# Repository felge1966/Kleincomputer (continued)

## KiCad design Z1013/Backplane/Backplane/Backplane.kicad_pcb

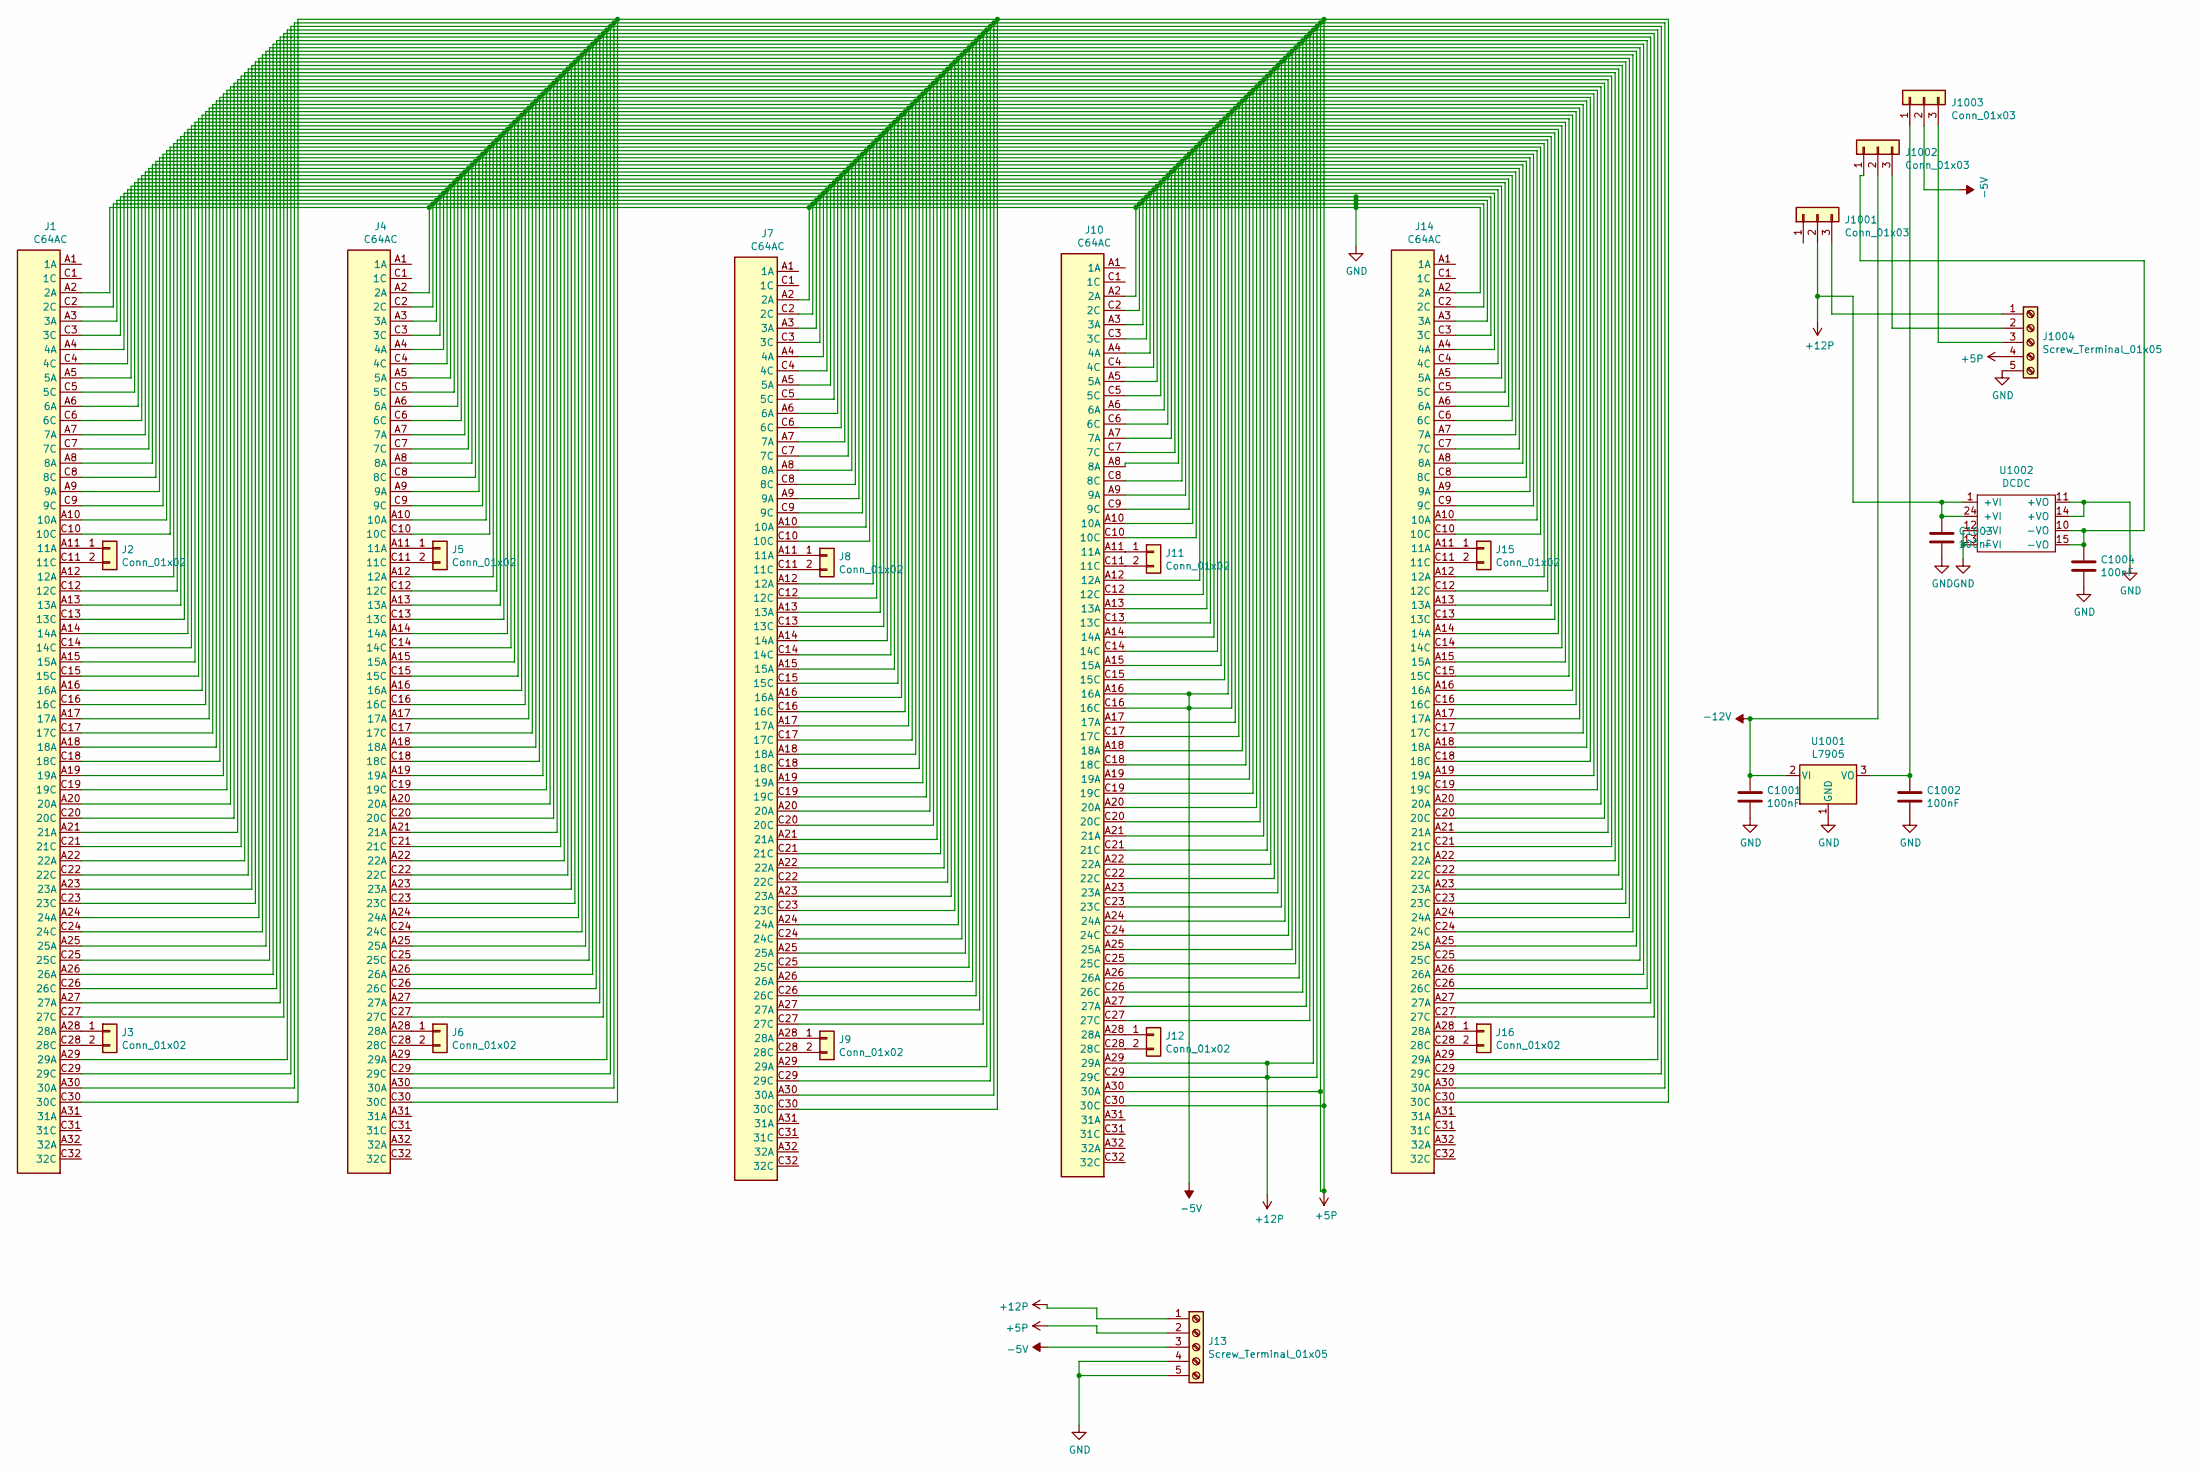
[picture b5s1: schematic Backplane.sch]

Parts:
C1001, C1002, C1003, C1004: 100nF; C_Disc_D3.0mm_W2.0mm_P2.50mm
J1, J4, J7, J10, J14: C64AC; DIN41612_C_3x32_Female_Vertical_THT-Gross_K1520
J2, J3, J5, J6, J8, J9, J11, J12, J15, J16: Conn_01x02; PinSocket_1x02_P2.54mm_Vertical
J13, J1004: Screw_Terminal_01x05; JST_EH_B5B-EH-A_1x05_P2.50mm_Vertical
J1001, J1002, J1003: Conn_01x03; PinHeader_1x03_P2.54mm_Vertical
U1001: L7905; TO-220-3_Horizontal_TabUp
U1002: DCDC; DIP-24_W15.24mm_LongPads

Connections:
+5P: J1.A30 (30A), J1.C30 (30C), J4.A30 (30A), J4.C30 (30C), J7.A30 (30A), J7.C30 (30C), J10.A30 (30A), J10.C30 (30C), J13.2, J14.A30 (30A), J14.C30 (30C), J1004.4
+12P: C1003.1, J1.A29 (29A), J1.C29 (29C), J4.A29 (29A), J4.C29 (29C), J7.A29 (29A), J7.C29 (29C), J10.A29 (29A), J10.C29 (29C), J13.1, J14.A29 (29A), J14.C29 (29C), J1001.2, U1002.1 (+VI), U1002.24 (+VI)
-5V: J1.A16 (16A), J1.C16 (16C), J4.A16 (16A), J4.C16 (16C), J7.A16 (16A), J7.C16 (16C), J10.A16 (16A), J10.C16 (16C), J13.3, J14.A16 (16A), J14.C16 (16C), J1003.2
-12V: C1001.1, J1002.2, U1001.2 (VI)
GND: C1001.2, C1002.2, C1003.2, C1004.2, J1.A2 (2A), J1.A3 (3A), J1.C2 (2C), J1.C3 (3C), J4.A2 (2A), J4.A3 (3A), J4.C2 (2C), J4.C3 (3C), J7.A2 (2A), J7.A3 (3A), J7.C2 (2C), J7.C3 (3C), J10.A2 (2A), J10.A3 (3A), J10.C2 (2C), J10.C3 (3C), J13.4, J13.5, J14.A2 (2A), J14.A3 (3A), J14.C2 (2C), J14.C3 (3C), J1004.5, U1001.1 (GND), U1002.11 (+VO), U1002.12 (-VI), U1002.13 (-VI), U1002.14 (+VO)
unnamed: C1002.1, J1003.1, U1001.3 (VO)
unnamed: C1004.1, J1002.1, U1002.10 (-VO), U1002.15 (-VO)
unnamed: J1.A4 (4A), J4.A4 (4A), J7.A4 (4A), J10.A4 (4A), J14.A4 (4A)
unnamed: J1.A5 (5A), J4.A5 (5A), J7.A5 (5A), J10.A5 (5A), J14.A5 (5A)
unnamed: J1.A6 (6A), J4.A6 (6A), J7.A6 (6A), J10.A6 (6A), J14.A6 (6A)
unnamed: J1.A7 (7A), J4.A7 (7A), J7.A7 (7A), J10.A7 (7A), J14.A7 (7A)
unnamed: J1.A8 (8A), J4.A8 (8A), J7.A8 (8A), J10.A8 (8A), J14.A8 (8A)
unnamed: J1.A9 (9A), J4.A9 (9A), J7.A9 (9A), J10.A9 (9A), J14.A9 (9A)
unnamed: J1.A10 (10A), J4.A10 (10A), J7.A10 (10A), J10.A10 (10A), J14.A10 (10A)
unnamed: J1.A11 (11A), J2.1
unnamed: J1.A12 (12A), J4.A12 (12A), J7.A12 (12A), J10.A12 (12A), J14.A12 (12A)
unnamed: J1.A13 (13A), J4.A13 (13A), J7.A13 (13A), J10.A13 (13A), J14.A13 (13A)
unnamed: J1.A14 (14A), J4.A14 (14A), J7.A14 (14A), J10.A14 (14A), J14.A14 (14A)
unnamed: J1.A15 (15A), J4.A15 (15A), J7.A15 (15A), J10.A15 (15A), J14.A15 (15A)
unnamed: J1.A17 (17A), J4.A17 (17A), J7.A17 (17A), J10.A17 (17A), J14.A17 (17A)
unnamed: J1.A18 (18A), J4.A18 (18A), J7.A18 (18A), J10.A18 (18A), J14.A18 (18A)
unnamed: J1.A19 (19A), J4.A19 (19A), J7.A19 (19A), J10.A19 (19A), J14.A19 (19A)
unnamed: J1.A20 (20A), J4.A20 (20A), J7.A20 (20A), J10.A20 (20A), J14.A20 (20A)
unnamed: J1.A21 (21A), J4.A21 (21A), J7.A21 (21A), J10.A21 (21A), J14.A21 (21A)
unnamed: J1.A22 (22A), J4.A22 (22A), J7.A22 (22A), J10.A22 (22A), J14.A22 (22A)
unnamed: J1.A23 (23A), J4.A23 (23A), J7.A23 (23A), J10.A23 (23A), J14.A23 (23A)
unnamed: J1.A24 (24A), J4.A24 (24A), J7.A24 (24A), J10.A24 (24A), J14.A24 (24A)
unnamed: J1.A25 (25A), J4.A25 (25A), J7.A25 (25A), J10.A25 (25A), J14.A25 (25A)
unnamed: J1.A26 (26A), J4.A26 (26A), J7.A26 (26A), J10.A26 (26A), J14.A26 (26A)
unnamed: J1.A27 (27A), J4.A27 (27A), J7.A27 (27A), J10.A27 (27A), J14.A27 (27A)
unnamed: J1.A28 (28A), J3.1
unnamed: J1.C4 (4C), J4.C4 (4C), J7.C4 (4C), J10.C4 (4C), J14.C4 (4C)
unnamed: J1.C5 (5C), J4.C5 (5C), J7.C5 (5C), J10.C5 (5C), J14.C5 (5C)
unnamed: J1.C6 (6C), J4.C6 (6C), J7.C6 (6C), J10.C6 (6C), J14.C6 (6C)
unnamed: J1.C7 (7C), J4.C7 (7C), J7.C7 (7C), J10.C7 (7C), J14.C7 (7C)
unnamed: J1.C8 (8C), J4.C8 (8C), J7.C8 (8C), J10.C8 (8C), J14.C8 (8C)
unnamed: J1.C9 (9C), J4.C9 (9C), J7.C9 (9C), J10.C9 (9C), J14.C9 (9C)
unnamed: J1.C10 (10C), J4.C10 (10C), J7.C10 (10C), J10.C10 (10C), J14.C10 (10C)
unnamed: J1.C11 (11C), J2.2
unnamed: J1.C12 (12C), J4.C12 (12C), J7.C12 (12C), J10.C12 (12C), J14.C12 (12C)
unnamed: J1.C13 (13C), J4.C13 (13C), J7.C13 (13C), J10.C13 (13C), J14.C13 (13C)
unnamed: J1.C14 (14C), J4.C14 (14C), J7.C14 (14C), J10.C14 (14C), J14.C14 (14C)
unnamed: J1.C15 (15C), J4.C15 (15C), J7.C15 (15C), J10.C15 (15C), J14.C15 (15C)
unnamed: J1.C17 (17C), J4.C17 (17C), J7.C17 (17C), J10.C17 (17C), J14.C17 (17C)
unnamed: J1.C18 (18C), J4.C18 (18C), J7.C18 (18C), J10.C18 (18C), J14.C18 (18C)
unnamed: J1.C19 (19C), J4.C19 (19C), J7.C19 (19C), J10.C19 (19C), J14.C19 (19C)
unnamed: J1.C20 (20C), J4.C20 (20C), J7.C20 (20C), J10.C20 (20C), J14.C20 (20C)
unnamed: J1.C21 (21C), J4.C21 (21C), J7.C21 (21C), J10.C21 (21C), J14.C21 (21C)
unnamed: J1.C22 (22C), J4.C22 (22C), J7.C22 (22C), J10.C22 (22C), J14.C22 (22C)
unnamed: J1.C23 (23C), J4.C23 (23C), J7.C23 (23C), J10.C23 (23C), J14.C23 (23C)
unnamed: J1.C24 (24C), J4.C24 (24C), J7.C24 (24C), J10.C24 (24C), J14.C24 (24C)
unnamed: J1.C25 (25C), J4.C25 (25C), J7.C25 (25C), J10.C25 (25C), J14.C25 (25C)
unnamed: J1.C26 (26C), J4.C26 (26C), J7.C26 (26C), J10.C26 (26C), J14.C26 (26C)
unnamed: J1.C27 (27C), J4.C27 (27C), J7.C27 (27C), J10.C27 (27C), J14.C27 (27C)
unnamed: J1.C28 (28C), J3.2
unnamed: J4.A11 (11A), J5.1
unnamed: J4.A28 (28A), J6.1
unnamed: J4.C11 (11C), J5.2
unnamed: J4.C28 (28C), J6.2
unnamed: J7.A11 (11A), J8.1
unnamed: J7.A28 (28A), J9.1
unnamed: J7.C11 (11C), J8.2
unnamed: J7.C28 (28C), J9.2
unnamed: J10.A11 (11A), J11.1
unnamed: J10.A28 (28A), J12.1
unnamed: J10.C11 (11C), J11.2
unnamed: J10.C28 (28C), J12.2
unnamed: J14.A11 (11A), J15.1
unnamed: J14.A28 (28A), J16.1
unnamed: J14.C11 (11C), J15.2
unnamed: J14.C28 (28C), J16.2
unnamed: J1001.3, J1004.1
unnamed: J1002.3, J1004.2
unnamed: J1003.3, J1004.3

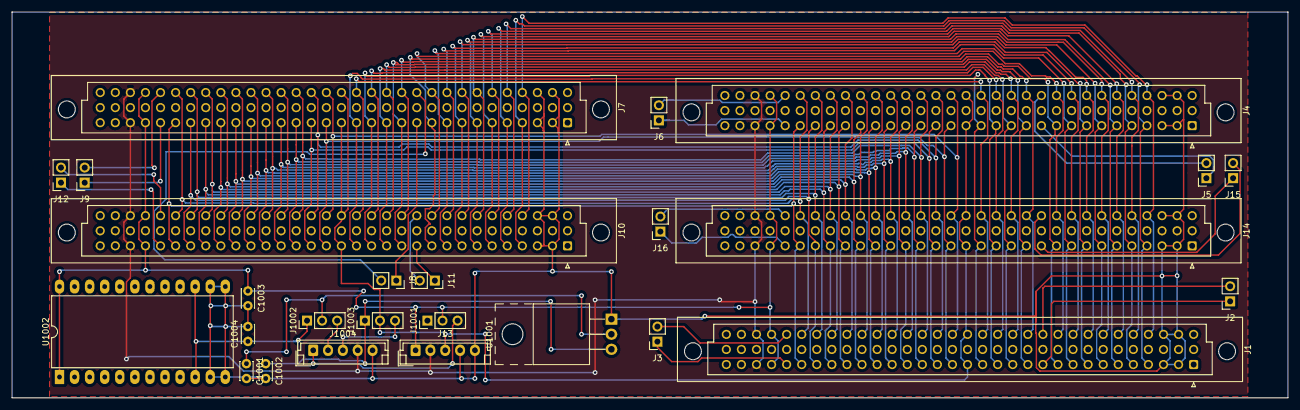
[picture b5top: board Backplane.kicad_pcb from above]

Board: 2 copper layers, 215.0 x 65.0 mm, 26 parts (0 on the bottom side), 74 nets.

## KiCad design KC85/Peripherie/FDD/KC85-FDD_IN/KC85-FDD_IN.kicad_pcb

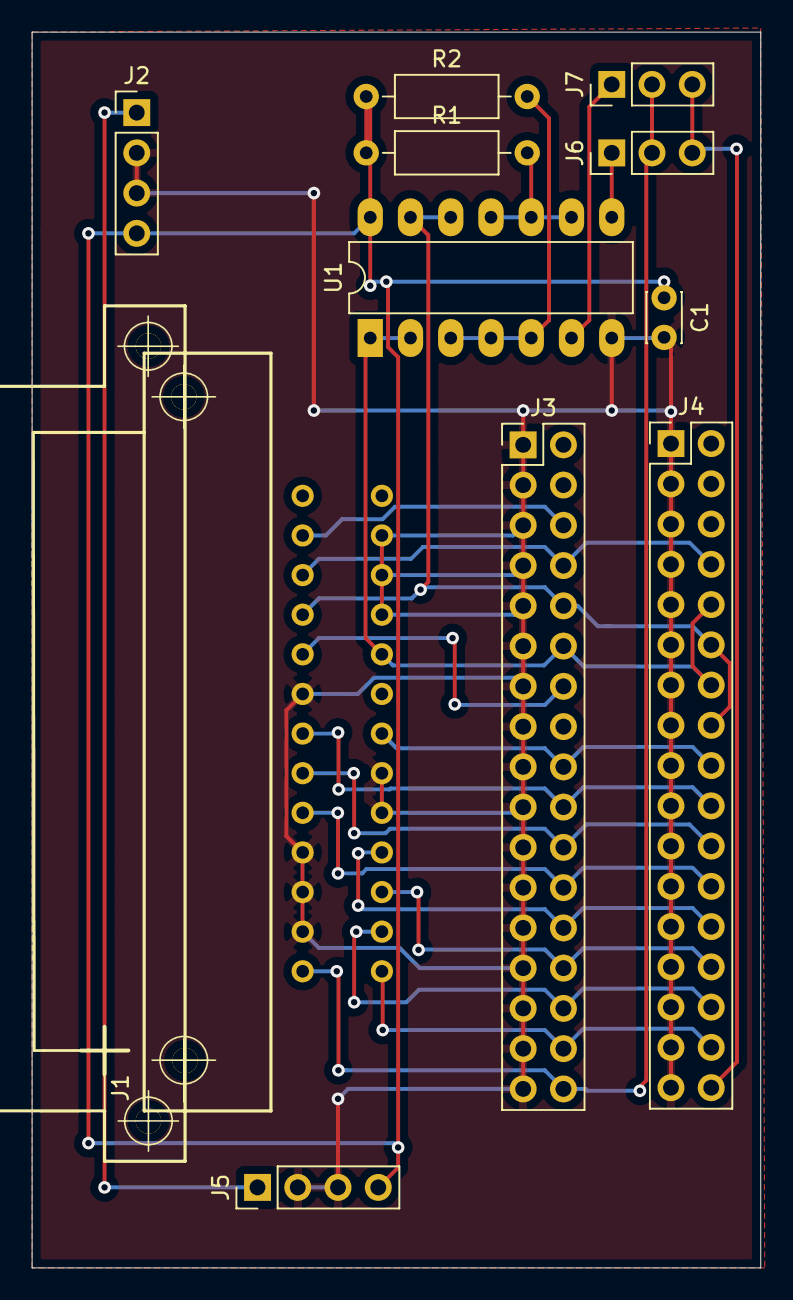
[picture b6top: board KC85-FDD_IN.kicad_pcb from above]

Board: 2 copper layers, 46.0 x 78.0 mm, 11 parts (0 on the bottom side), 22 nets.

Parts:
C1: 100n; C_Disc_D3.0mm_W2.0mm_P2.50mm
J1: Conn_02x13_Row_Letter_First; EFS2x13_DIN_male_a1
J2, J5: Conn_01x04; PinHeader_1x04_P2.54mm_Vertical
J3: IC; PinHeader_2x17_P2.54mm_Vertical
J4: Drive; PinHeader_2x17_P2.54mm_Vertical
J6: RDY-SE0; PinHeader_1x03_P2.54mm_Vertical
J7: RDY-SE1; PinHeader_1x03_P2.54mm_Vertical
R1, R2: 1K; R_Axial_DIN0207_L6.3mm_D2.5mm_P10.16mm_Horizontal
U1: 74LS03; DIP-14_W7.62mm_LongPads

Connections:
+5P: C1.1, J2.4, J5.4, R1.1, R2.1, U1.14
+12P: J2.1, J5.1
GND: C1.2, J1.a6, J1.a10, J1.a11, J1.a12, J1.b2, J1.b3, J1.b4, J1.b8, J1.b9, J2.2, J2.3, J3.1, J3.3, J3.5, J3.7, J3.9, J3.11, J3.13, J3.15, J3.17, J3.19, J3.21, J3.23, J3.25, J3.27, J3.29, J3.31, J3.33, J4.1, J4.3, J4.5, J4.7, J4.9, J4.11, J4.13, J4.15, J4.17, J4.19, J4.21, J4.23, J4.25, J4.27, J4.29, J4.31, J4.33, J5.2, J5.3, U1.7
IX: J1.a3, J3.8, J4.8
unnamed: J4.34, J6.3, J7.3
unnamed: J6.1, U1.8
unnamed: J7.1, U1.6
unnamed: R1.2, U1.9, U1.10, U1.11
unnamed: R2.2, U1.3, U1.4, U1.5
RD: J1.b12, J3.30, J4.30
RDY: J1.a13, J3.34, J6.2, J7.2
SD: J1.b7, J3.18, J4.18
SE0: J1.a4, J3.10, J4.12, J4.16, U1.12, U1.13
SE1: J1.b5, J3.12, J4.10, J4.14, U1.1, U1.2
SE2: J1.a5, J3.14
SE3: J1.a2, J3.6
SS: J1.b13, J3.32, J4.32
ST: J1.a7, J3.20, J4.20
T0: J1.b10, J3.26, J4.26
WD: J1.a8, J3.22, J4.22
WE: J1.a9, J3.24, J4.24
WP: J1.b11, J3.28, J4.28

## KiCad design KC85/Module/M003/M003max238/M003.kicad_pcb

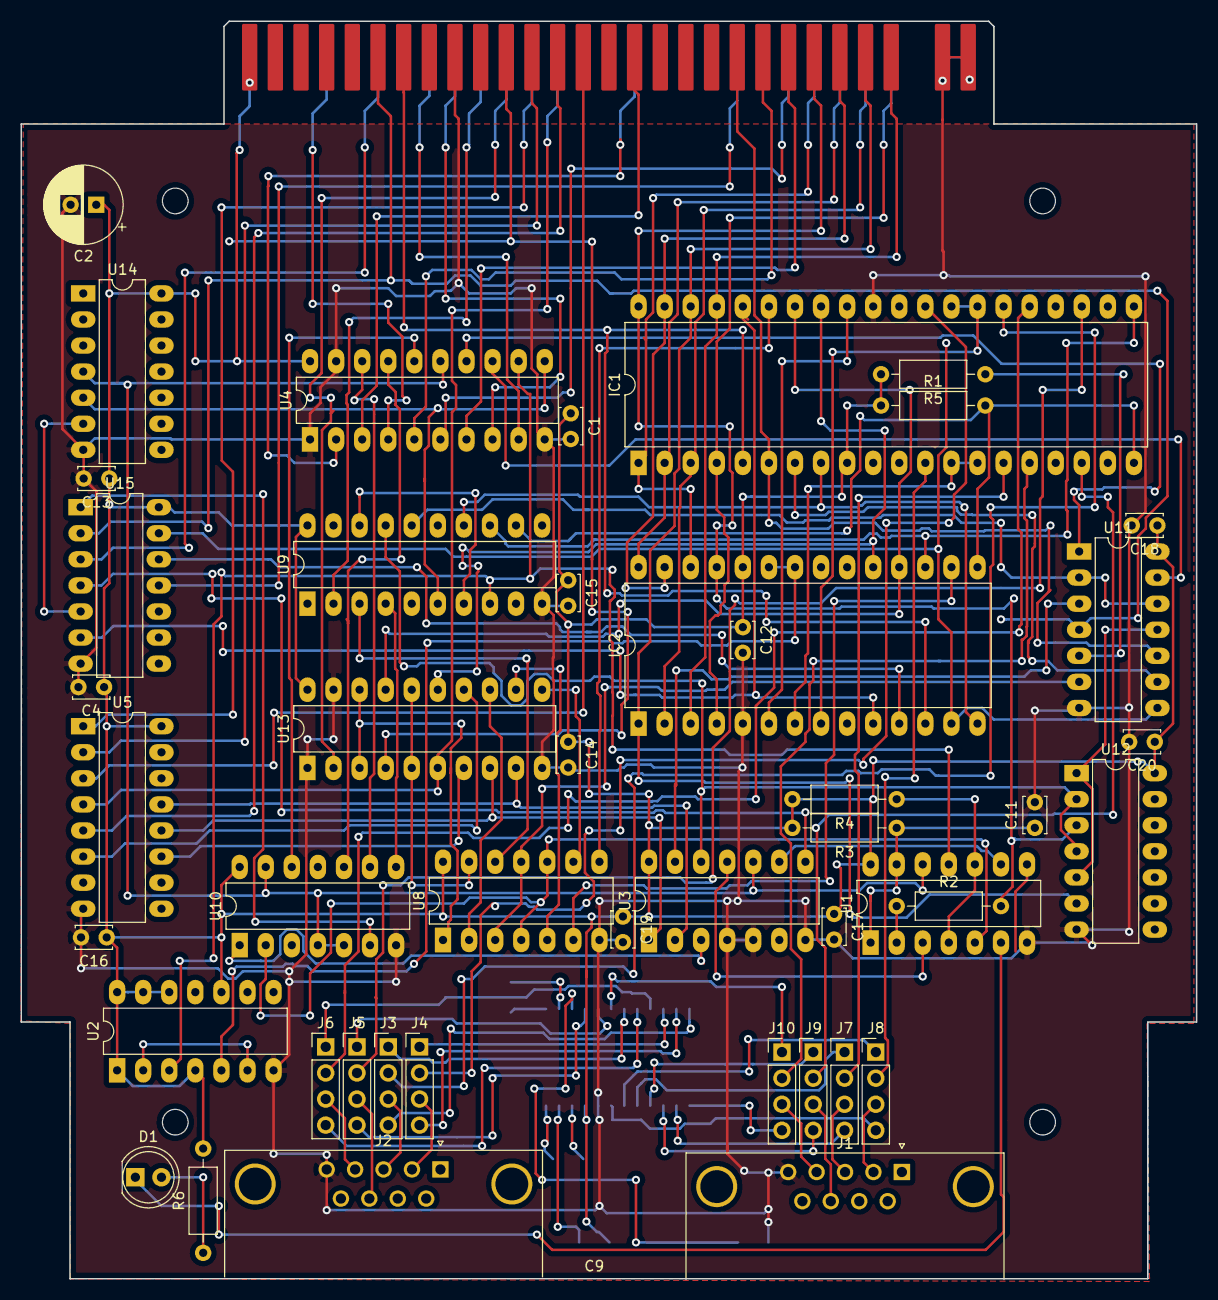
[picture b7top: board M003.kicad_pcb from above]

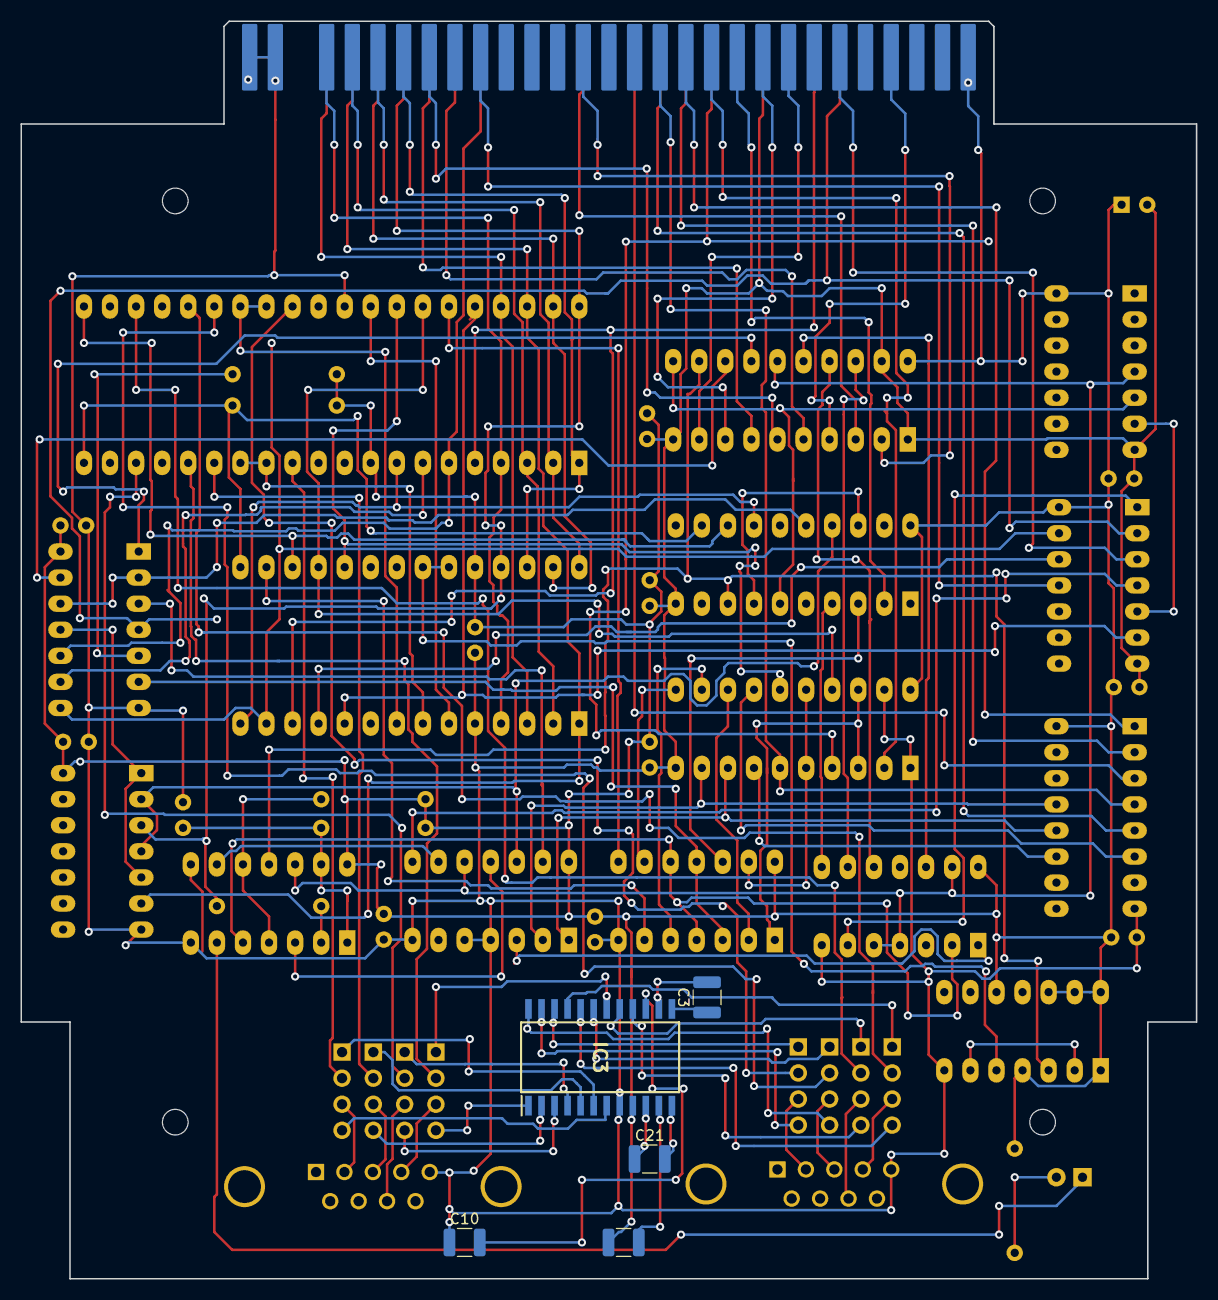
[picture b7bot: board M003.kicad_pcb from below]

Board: 2 copper layers, 114.5 x 122.5 mm, 51 parts (5 on the bottom side), 123 nets.

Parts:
C1, C4, C12, C13, C14, C15, C16, C17, C18, C19, C20: 22nF; C_Disc_D3.4mm_W2.1mm_P2.50mm
C2: 560µ; CP_Radial_D7.5mm_P2.50mm
C3, C9, C10, C21: 1µ; C_1210_3225Metric
C11: 100n; C_Disc_D3.4mm_W2.1mm_P2.50mm
D1: LED; LED_D5.0mm
IC1: SIO2-DIP-40; DIP-40_W15.24mm_LongPads
IC2: CTC-DIP-28; DIP-28_W15.24mm_LongPads
IC3: MAX238CWG+; SOIC127P1032X265-24N
J1: SER1; DSUB-9_Female_Horizontal_P2.77x2.84mm_EdgePinOffset7.70mm_H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
J2: SER2; DSUB-9_Female_Horizontal_P2.77x2.84mm_EdgePinOffset7.70mm_H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
J3: TXD2; PinHeader_1x04_P2.54mm_Vertical
J4: RxD2; PinHeader_1x04_P2.54mm_Vertical
J5: CTS2; PinHeader_1x04_P2.54mm_Vertical
J6: DTR2; PinHeader_1x04_P2.54mm_Vertical
J7: TXD1; PinHeader_1x04_P2.54mm_Vertical
J8: RxD1; PinHeader_1x04_P2.54mm_Vertical
J9: CTS1; PinHeader_1x04_P2.54mm_Vertical
J10: DTR1; PinHeader_1x04_P2.54mm_Vertical
R1: 620; R_Axial_DIN0207_L6.3mm_D2.5mm_P10.16mm_Horizontal
R2: 100R; R_Axial_DIN0207_L6.3mm_D2.5mm_P10.16mm_Horizontal
R3, R4, R5: 2K2; R_Axial_DIN0207_L6.3mm_D2.5mm_P10.16mm_Horizontal
R6: 390R; R_Axial_DIN0207_L6.3mm_D2.5mm_P10.16mm_Horizontal
U1, U2: 74LS74; DIP-14_W7.62mm_LongPads
U3, U14: 74LS00; DIP-14_W7.62mm_LongPads
U4, U9, U13: 74LS540; DIP-20_W7.62mm_LongPads
U5: 74LS138; DIP-16_W7.62mm_LongPads
U8: 74LS10; DIP-14_W7.62mm_LongPads
U10: 74LS20; DIP-14_W7.62mm_LongPads
U11, U15: 74LS08; DIP-14_W7.62mm_LongPads
U12: 74LS03; DIP-14_W7.62mm_LongPads
XM1: KC85_Modulsteckverbinder; KC85_Modul

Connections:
+5P: C1.1, C2.1, C4.1, C9.2, C12.1, C13.1, C14.1, C15.1, C16.1, C17.1, C18.1, C19.1, C20.1, IC1.9, IC2.24, IC3.9, R1.1, R3.2, R4.2, R5.2, R6.2, U1.14, U2.1, U2.4, U2.10, U2.12, U2.13, U2.14, U3.14, U4.20, U5.16, U8.14, U9.20, U10.14, U11.14, U12.14, U13.20, U14.14, U15.14, XM1.29A, XM1.29B
AB0: U13.2, XM1.19A
AB1: U13.4, XM1.19B
AB2: U5.1, XM1.18A
AB3: U5.2, XM1.18B
AB4: U5.4, U13.6, XM1.17A
AB5: U5.5, XM1.17B
AB7: U5.3, XM1.16B
AB8: U4.2, XM1.14A
AB9: U4.3, XM1.14B
CTSA: IC1.18, J9.2
CTSB: IC1.23, J5.2
DB0: IC1.40, IC2.25, R2.2, U12.3, XM1.7B
DB1: IC1.1, IC2.26, XM1.7A
DB2: IC1.39, IC2.27, XM1.6B
DB3: IC1.2, IC2.28, XM1.6A
DB4: IC1.38, IC2.1, U12.6, XM1.5B
DB5: IC1.3, IC2.2, XM1.5A
DB6: IC1.37, IC2.3, XM1.4B
DB7: IC1.4, IC2.4, XM1.4A
DTRA: IC1.16, J10.2
DTRB: IC1.25, J6.2
GND: C1.2, C2.2, C4.2, C10.1, C11.2, C12.2, C13.2, C14.2, C15.2, C16.2, C17.2, C18.2, C19.2, C20.2, IC1.31, IC2.5, IC3.8, J1.5, J2.5, U1.7, U2.7, U3.4, U3.5, U3.7, U4.1, U4.10, U4.19, U5.8, U8.7, U9.10, U10.7, U11.7, U12.7, U13.1, U13.10, U13.19, U14.7, U15.7, XM1.1A, XM1.1B, XM1.2A, XM1.2B, XM1.21B
IEI: IC1.6, U11.10, XM1.10B
IEO: U15.11, XM1.10A
MEI: U11.4, U15.2, XM1.24B
MEO: U15.3, XM1.24A
N09: U1.12, U3.10, U4.15, U10.4, U10.5, U10.13, U14.4
N12: IC1.32, IC2.6
N13: IC1.20, IC2.15, R1.2, U9.12
N14: U14.6, U15.5
N15: IC1.8, IC2.14, U9.14
N16: IC1.21, IC2.17, U9.13
N20: IC1.34, IC2.18, U13.17
N21: IC1.33, IC2.19, U13.15
N24: U1.11, U2.3, U4.12, U9.8
N25: IC1.36, IC2.10, U15.6
N33: IC2.22, IC2.23, U2.5
unnamed: C3.1, IC3.13
unnamed: C3.2, IC3.14
unnamed: C9.1, IC3.11
unnamed: C10.2, IC3.15
unnamed: C11.1, R3.1, U1.1, U1.13
unnamed: C21.1, IC3.10
unnamed: C21.2, IC3.12
unnamed: D1.1, U1.6
unnamed: D1.2, R6.1
unnamed: IC1.7, U11.9
unnamed: IC1.13, IC1.14, IC2.7
unnamed: IC1.27, IC1.28, IC2.8
unnamed: IC1.35, U8.8
unnamed: IC2.11, U15.12
unnamed: IC2.13, U11.8, U15.13
unnamed: IC2.16, U8.6
unnamed: IC3.1, J10.4
unnamed: IC3.2, J7.4
unnamed: IC3.3, J9.4
unnamed: IC3.4, J9.1
unnamed: IC3.5, J7.1
unnamed: IC3.6, J8.1
unnamed: IC3.7, J8.4
unnamed: IC3.16, J5.4
unnamed: IC3.17, J5.1
unnamed: IC3.18, J10.1
unnamed: IC3.19, J3.1
unnamed: IC3.20, J6.4
unnamed: IC3.21, J6.1
unnamed: IC3.22, J4.1
unnamed: IC3.23, J4.4
unnamed: IC3.24, J3.4
unnamed: J1.2, J8.3
unnamed: J1.3, J7.3
unnamed: J1.4, J10.3
unnamed: J1.8, J9.3
unnamed: J2.2, J4.3
unnamed: J2.3, J3.3
unnamed: J2.4, J6.3
unnamed: J2.8, J5.3
unnamed: R2.1, U1.2
unnamed: R4.1, U1.4, U1.10
unnamed: R5.1, U11.5
unnamed: U1.3, U3.11
unnamed: U1.5, U8.4, U8.10, U10.2
unnamed: U1.9, U3.9
unnamed: U2.2, U2.6
unnamed: U8.12, U9.3
unnamed: U9.7, U9.18
unnamed: U3.3, U10.1
unnamed: U10.6, U15.1
unnamed: U9.4, U10.8
unnamed: U4.18, U10.9
unnamed: U4.17, U10.10
unnamed: U4.16, U10.12
unnamed: U4.14, U11.1
unnamed: U3.13, U11.3
unnamed: U8.3, U8.11, U11.6
unnamed: U11.11, U12.1, U12.5
unnamed: U9.16, U11.2, U11.12
unnamed: U4.13, U11.13
unnamed: U3.12, U9.17, U12.2, U12.4
unnamed: U5.11, U13.7
unnamed: U3.1, U5.12, U13.8
unnamed: U3.2, U5.13, U13.9
unnamed: U8.9, U13.11
unnamed: U8.5, U13.12
unnamed: U8.2, U13.13
unnamed: U5.6, U13.14
unnamed: U8.13, U13.5, U13.16
unnamed: U8.1, U13.3, U13.18
unnamed: U4.11, U9.6, U14.5
unnamed: U3.8, U15.4
RXDA: IC1.12, J8.2
RXDB: IC1.29, J4.2
TAKT: U4.8, XM1.21A
TXDA: IC1.15, J7.2
TXDB: IC1.26, J3.2
~INT: IC1.5, IC2.12, XM1.23B
~IORQ: U4.5, XM1.9B
~M1: U4.9, XM1.22A
~MAD: U4.4, XM1.26A
~RD: U4.7, XM1.8B
~RESET: U9.2, XM1.20A
~WR: U4.6, XM1.8A

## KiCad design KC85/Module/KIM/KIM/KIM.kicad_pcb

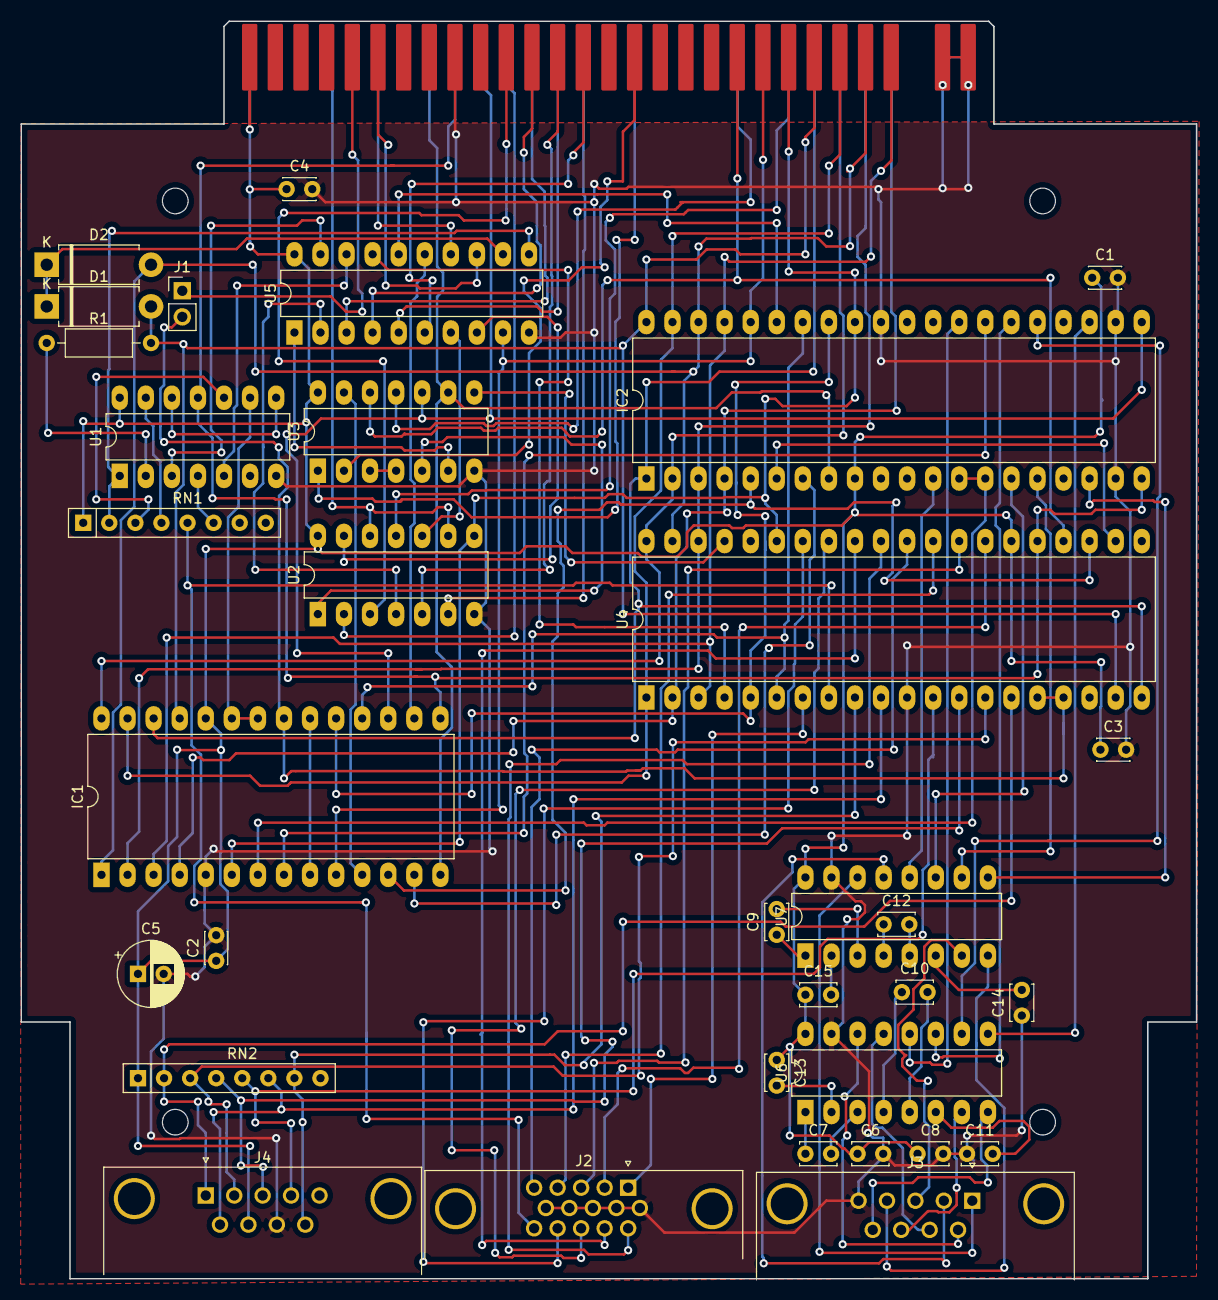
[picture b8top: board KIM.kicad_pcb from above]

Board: 2 copper layers, 114.5 x 122.5 mm, 34 parts (0 on the bottom side), 106 nets.

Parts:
C1, C2, C3, C4: 100n; C_Disc_D3.0mm_W2.0mm_P2.50mm
C5: 560µ; CP_Radial_D6.3mm_P2.50mm
C6, C7, C8, C9, C10, C11, C12, C13, C14, C15: 1µ; C_Disc_D3.4mm_W2.1mm_P2.50mm
D1, D2: GA104; D_DO-15_P10.16mm_Horizontal
IC1: CTC-DIP-28; DIP-28_W15.24mm_LongPads
IC2: SIO0-DIP-40; DIP-40_W15.24mm_LongPads
J1: Conn_01x02; PinHeader_1x02_P2.54mm_Vertical
J2: LPT; DSUB-15-HD_Female_Horizontal_P2.29x1.98mm_EdgePinOffset3.03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
J3: Dual_V24; DSUB-9_Female_Horizontal_P2.77x2.84mm_EdgePinOffset4.94mm_H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
J4: Joy; DSUB-9_Male_Horizontal_P2.77x2.84mm_EdgePinOffset4.94mm_Hou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
R1: 100; R_Axial_DIN0207_L6.3mm_D2.5mm_P10.16mm_Horizontal
RN1, RN2: 3K9; R_Array_SIP8
U1: 74LS74; DIP-14_W7.62mm_LongPads
U2: 74LS02; DIP-14_W7.62mm_LongPads
U3: 74LS08; DIP-14_W7.62mm_LongPads
U4: Z80PIO; DIP-40_W15.24mm_LongPads
U5: GAL16V8; DIP-20_W7.62mm_LongPads
U6, U7: MAX232I; DIP-16_W7.62mm_LongPads
XM1: KC85_Modulsteckverbinder; KC85_Modul

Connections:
+5P: C1.1, C2.1, C3.1, C4.1, C5.1, C6.1, C8.1, C13.1, C15.1, IC1.24, IC2.9, J4.7, RN1.1, RN2.1, U1.14, U2.14, U3.14, U4.26, U5.20, U6.16, U7.16, XM1.29A, XM1.29B
A0: IC1.18, IC2.34, U4.6
A1: IC1.19, IC2.33, U4.5
AB0: U2.2, XM1.19A
AB1: U2.3, XM1.19B
AB2: U5.3, XM1.18A
AB3: U5.4, XM1.18B
AB4: U5.5, XM1.17A
AB5: U2.5, XM1.17B
AB6: U2.6, XM1.16A
AB7: U5.6, XM1.16B
AB8: U3.1, XM1.14A
AB9: U3.2, XM1.14B
DB0: D1.2, IC1.25, IC2.40, R1.2, U4.19, XM1.7B
DB1: IC1.26, IC2.1, U4.20, XM1.7A
DB2: IC1.27, IC2.39, U4.1, XM1.6B
DB3: IC1.28, IC2.2, U4.40, XM1.6A
DB4: D2.2, IC1.1, IC2.38, U4.39, XM1.5B
DB5: IC1.2, IC2.3, U4.38, XM1.5A
DB6: IC1.3, IC2.37, U4.3, XM1.4B
DB7: IC1.4, IC2.4, U4.2, XM1.4A
GND: C1.2, C2.2, C3.2, C4.2, C5.2, C6.2, C8.2, C11.1, C14.1, IC1.5, IC2.19, IC2.22, IC2.31, J2.6, J2.7, J2.8, J2.9, J2.10, J3.5, J4.8, U1.7, U2.7, U3.7, U4.11, U5.10, U6.15, U7.15, XM1.1A, XM1.1B, XM1.2A, XM1.2B, XM1.21B
IEI: U3.12, U4.24, XM1.10B
IEO: U3.11, XM1.10A
MEI: U5.13, XM1.24B
MEO: U5.14, XM1.24A
unnamed: C7.1, U6.1
unnamed: C7.2, U6.3
unnamed: C9.1, U7.1
unnamed: C9.2, U7.3
unnamed: C10.1, U6.4
unnamed: C10.2, U6.5
unnamed: C11.2, U6.6
unnamed: C12.1, U7.4
unnamed: C12.2, U7.5
unnamed: C13.2, U6.2
unnamed: C14.2, U7.6
unnamed: C15.2, U7.2
unnamed: D1.1, D2.1, U5.12
unnamed: IC1.7, IC2.13, IC2.14
unnamed: IC1.8, IC2.27
unnamed: IC1.11, U3.13
unnamed: IC1.13, IC2.7
unnamed: IC1.16, U5.15
unnamed: IC1.9, IC1.20
unnamed: IC1.21, J1.2, U4.16, U4.17
unnamed: IC1.22, IC1.23, U1.9
unnamed: IC2.6, U4.22
unnamed: IC2.12, U7.12
unnamed: IC2.15, U7.11
unnamed: IC2.16, U7.10
unnamed: IC2.18, U7.9
unnamed: IC2.23, U6.9
unnamed: IC2.25, U6.10
unnamed: IC2.26, U6.11
unnamed: IC2.28, U6.12
unnamed: IC2.35, U5.16
unnamed: J2.1, U4.7
unnamed: J2.2, U4.27
unnamed: J2.3, U4.28
unnamed: J2.4, U4.29
unnamed: J2.5, U4.30
unnamed: J2.11, U4.31
unnamed: J2.12, U4.32
unnamed: J2.13, U4.33
unnamed: J2.14, U4.34
unnamed: J2.15, RN1.5, U4.8
unnamed: J3.1, U7.14
unnamed: J3.2, U7.13
unnamed: J3.3, U7.7
unnamed: J3.4, U7.8
unnamed: J3.6, U6.14
unnamed: J3.7, U6.13
unnamed: J3.8, U6.7
unnamed: J3.9, U6.8
unnamed: J4.1, RN2.2, U4.15
unnamed: J4.2, RN2.3, U4.14
unnamed: J4.3, RN2.4, U4.13
unnamed: J4.4, RN2.5, U4.12
unnamed: J4.6, RN2.6, U4.10
unnamed: J4.9, RN2.7, U4.9
unnamed: R1.1, U1.2
unnamed: RN1.2, U1.1, U5.11
unnamed: RN1.3, U1.10
unnamed: RN1.4, U1.13
unnamed: RN1.6, U1.4
unnamed: U1.3, U5.19
unnamed: U1.5, U5.18
unnamed: U1.8, U1.12
unnamed: U2.1, U3.5
unnamed: U2.4, U5.2
unnamed: U2.10, U5.7
unnamed: U2.13, U5.8
unnamed: U3.3, U3.4
unnamed: U3.6, U5.1
unnamed: U3.8, U4.37
unnamed: U4.4, U5.17
TAKT: IC1.15, IC2.20, U1.11, U4.25, XM1.21A
~BI: J1.1, XM1.25B
~INT: IC1.12, IC2.5, U4.23
~IORQ: IC1.10, IC2.36, U5.9, XM1.9B
~M1: IC1.14, IC2.8, U3.9, XM1.22A
~MAD: U2.9, U2.12, XM1.26A
~RD: IC1.6, IC2.32, U2.8, U4.35, XM1.8B
~RESET: IC1.17, IC2.21, U3.10, XM1.20A
~WR: U2.11, XM1.8A

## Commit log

2025-07-21 Create Jumper
2025-07-21 Rename Jumper to Jumper.md
2026-02-20 Create Readme for RAF2014 to RAF512 modification
    Added detailed instructions for modifying RAF2014 to RAF512, including RAM addressing, new decoding, and control port information.
2026-02-20 Add project and software information to README
2026-02-20 Revise RAM addressing and wiring instructions
    Updated RAM addressing and connection instructions in Readme.
2026-02-20 Update README formatting and headings
2026-02-20 Fix formatting in README for project list
2026-02-20 Modify README for SD-Interface details
    Updated the README to reflect the SD-Interface for Z1013.
2026-02-20 Update README with SD card integration details
    Removed outdated information about using a cassette deck and added details about the new SD card integration with the Z1013, including the use of a Raspberry Pico for data handling.
2026-02-20 Update README with new image link and SD card usage
    Updated image link in README and added information about using SD card for program storage.
2026-02-20 Add AC1 project to README
2026-02-20 Update README with new hardware entries
    Added Polycomputer Poly880 and LC80 to the list.
